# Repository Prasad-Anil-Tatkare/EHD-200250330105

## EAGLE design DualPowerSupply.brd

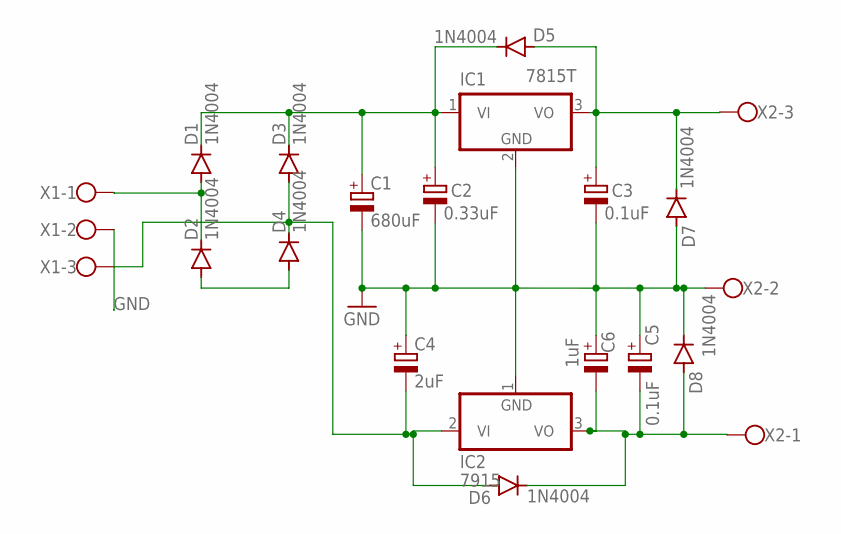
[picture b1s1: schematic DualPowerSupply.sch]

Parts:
C1: 680uF; B45181B
C2: 0.33uF; E2-4
C3, C5: 0.1uF; E2-4
C4: 2uF; E2-4
C6: 1uF; E2-4
D1, D2, D3, D4, D5, D6, D7, D8: 1N4004; DO41-10
IC1: 7815T; TO220H
IC2: 7915; TO220H
X1, X2: W237-103

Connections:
GND: C1.-, C2.-, C3.-, C4.+, C5.+, C6.+, D7.A, D8.C, IC1.2 (GND), IC2.1 (GND), X1.2, X2.2
unnamed: C3.+, D5.A, D7.C, IC1.3 (VO), X2.3
unnamed: C1.+, C2.+, D1.C, D3.C, D5.C, IC1.1 (VI)
unnamed: C4.-, D3.A, D4.C, D6.A, IC2.2 (VI), X1.3
unnamed: D2.A, D4.A
unnamed: D1.A, D2.C, X1.1
unnamed: C5.-, C6.-, D6.C, D8.A, IC2.3 (VO), X2.1

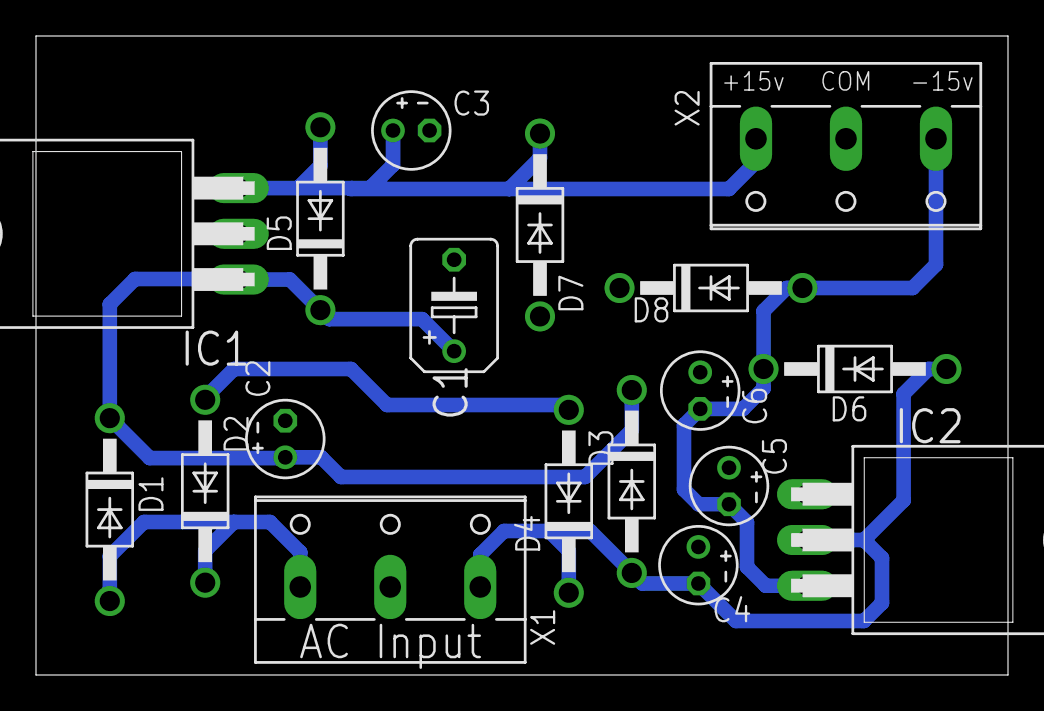
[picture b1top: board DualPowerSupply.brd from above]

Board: 2 copper layers, 54.0 x 35.5 mm, 18 parts (0 on the bottom side), 7 nets.

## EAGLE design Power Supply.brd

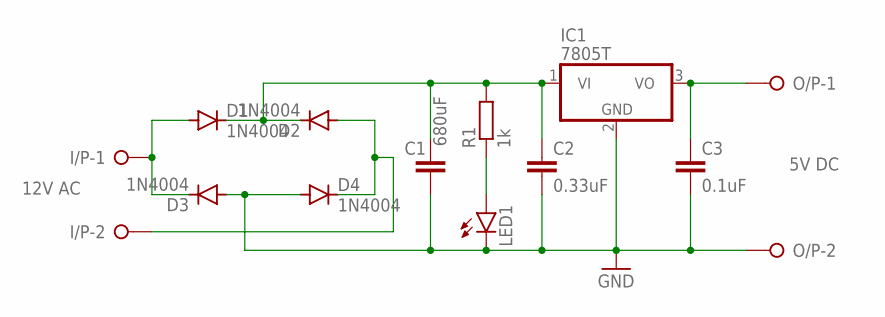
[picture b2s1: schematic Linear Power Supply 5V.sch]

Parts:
C1: 680uF; C025-060X050
C2: 0.33uF; C025-060X050
C3: 0.1uF; C025-060X050
D1, D2, D3, D4: 1N4004; DO41-10
I/P: 12V AC; W237-132
IC1: 7805T; TO220H
LED1: LED3MM
O/P: 5V DC; W237-132
R1: 1k; 0207/12

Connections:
GND: C1.2, C2.2, C3.2, D3.A, D4.A, IC1.2 (GND), LED1.K (C), O/P.2
unnamed: D1.A, D3.C, I/P.1
unnamed: C1.1, C2.1, D1.C, D2.C, IC1.1 (VI), R1.2
unnamed: LED1.A, R1.1
unnamed: C3.1, IC1.3 (VO), O/P.1
unnamed: D2.A, D4.C, I/P.2

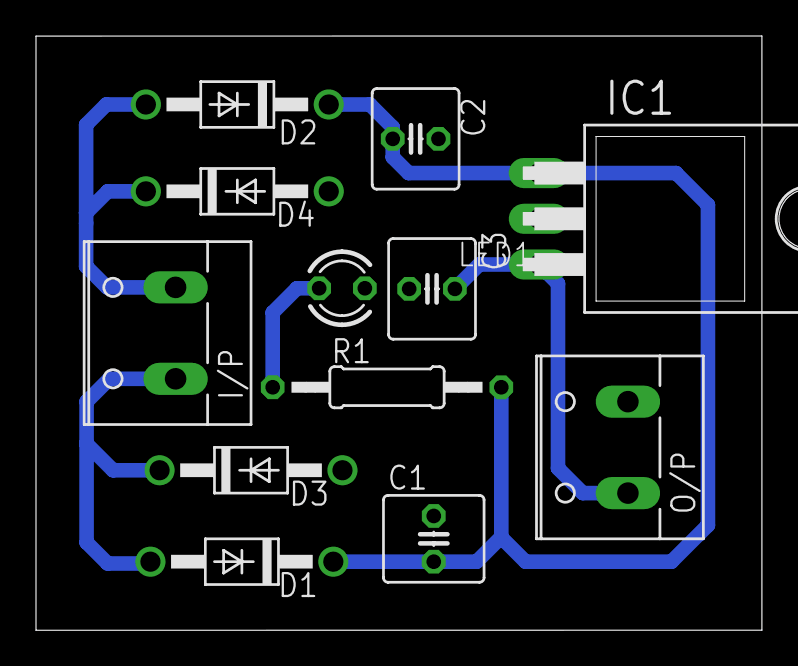
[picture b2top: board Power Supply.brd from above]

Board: 2 copper layers, 40.3 x 33.0 mm, 12 parts (0 on the bottom side), 6 nets.
